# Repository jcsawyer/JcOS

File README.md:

Raspberry PI OS Tutorials translated from the Rust tutorials available [here](https://github.com/rust-embedded/rust-raspberrypi-OS-tutorials/tree/master)

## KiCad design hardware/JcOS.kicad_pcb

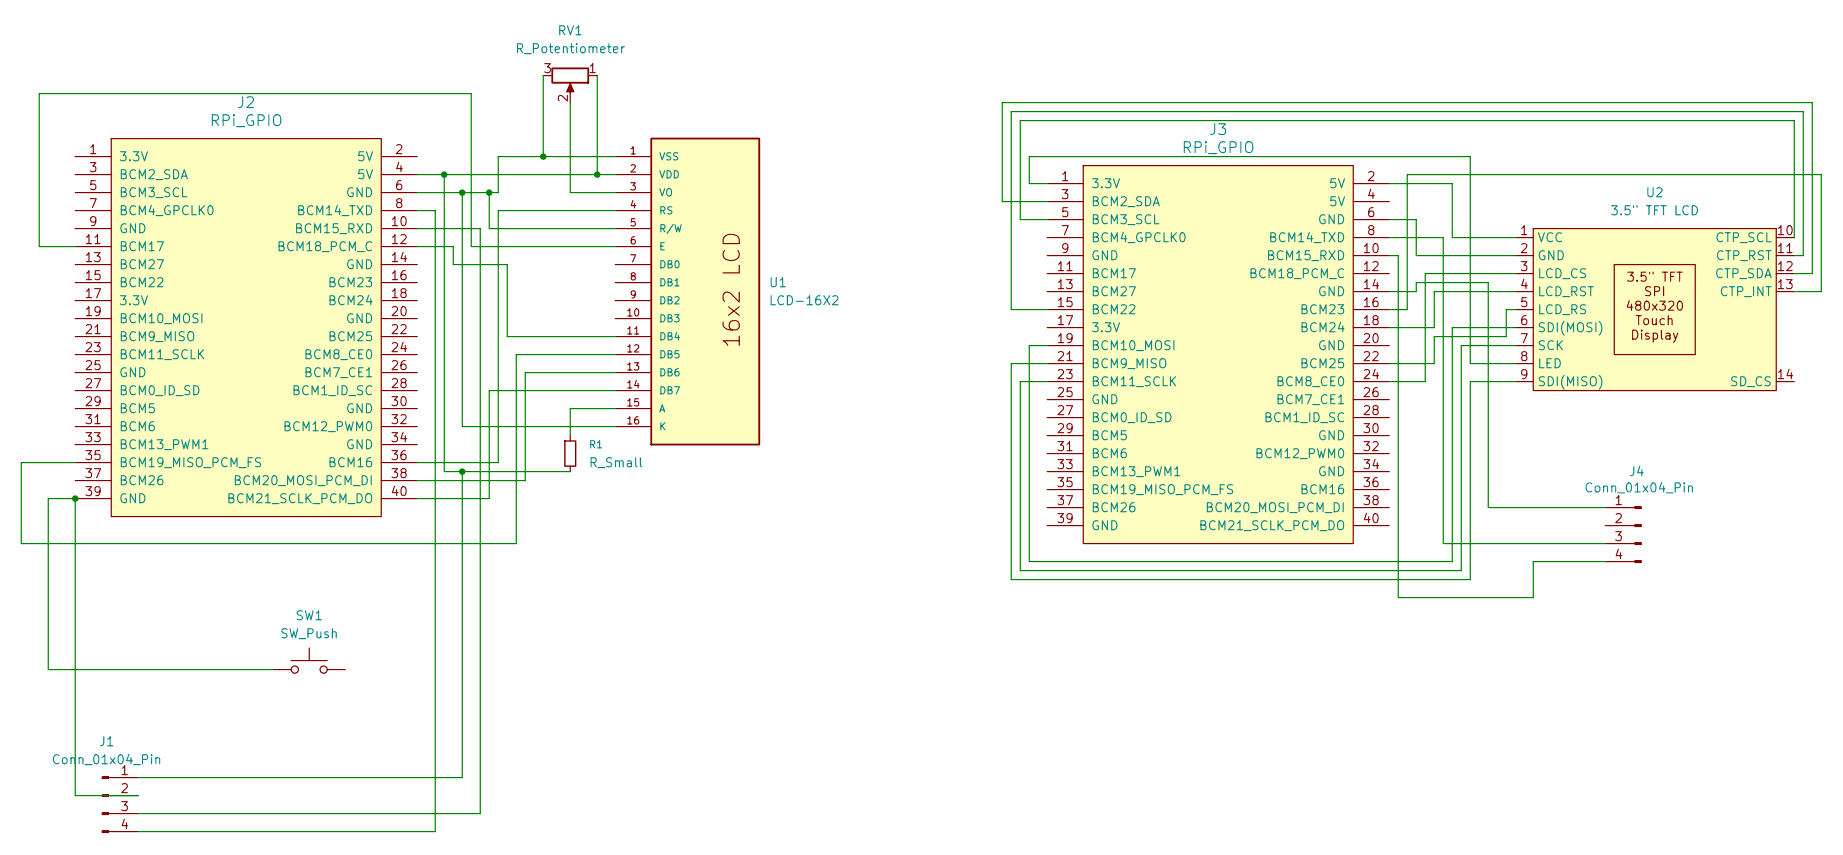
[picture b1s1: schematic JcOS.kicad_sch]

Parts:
J1, J4: Conn_01x04_Pin; PinHeader_1x04_P2.54mm_Vertical
J2, J3: RPi_GPIO; RPI_Hat_B+
R1: R_Small; R_Axial_DIN0309_L9.0mm_D3.2mm_P12.70mm_Horizontal
RV1: R_Potentiometer; Potentiometer_Bourns_3386F_Vertical
SW1: SW_Push; SW_PUSH_6mm
U1: LCD-16X2; MODULE_LCD-16X2; PARTREV N/A
U2: 3.5" TFT LCD; 3.5_ TFT LCD

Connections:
unnamed: J1.1, J2.4 (5V), R1.2, RV1.1, U1.2 (VDD)
unnamed: J1.2, J2.39 (GND), SW1.1
unnamed: J1.3, J2.10 (BCM15_RXD)
unnamed: J1.4, J2.8 (BCM14_TXD)
unnamed: J2.36 (BCM16), U1.4 (RS)
unnamed: J2.11 (BCM17), U1.6 (E)
unnamed: J2.12 (BCM18_PCM_C), U1.11 (DB4)
unnamed: J2.35 (BCM19_MISO_PCM_FS), U1.12 (DB5)
unnamed: J2.38 (BCM20_MOSI_PCM_DI), U1.13 (DB6)
unnamed: J2.40 (BCM21_SCLK_PCM_DO), U1.14 (DB7)
unnamed: J3.3 (BCM2_SDA), U2.12 (CTP_SDA)
unnamed: J3.5 (BCM3_SCL), U2.10 (CTP_SCL)
unnamed: J3.24 (BCM8_CE0), U2.3 (LCD_CS)
unnamed: J3.21 (BCM9_MISO), U2.9 (SDI(MISO))
unnamed: J3.19 (BCM10_MOSI), U2.6 (SDI(MOSI))
unnamed: J3.23 (BCM11_SCLK), U2.7 (SCK)
unnamed: J3.8 (BCM14_TXD), J4.3
unnamed: J3.10 (BCM15_RXD), J4.4
unnamed: J3.15 (BCM22), U2.11 (CTP_RST)
unnamed: J3.16 (BCM23), U2.13 (CTP_INT)
unnamed: J3.18 (BCM24), U2.4 (LCD_RST)
unnamed: J3.22 (BCM25), U2.5 (LCD_RS)
unnamed: J3.14 (GND), J4.1
unnamed: R1.1, U1.15 (A)
unnamed: J2.6 (GND), RV1.3, U1.1 (VSS), U1.5 (R/W), U1.16 (K)
unnamed: RV1.2, U1.3 (VO)
unnamed: J3.6 (GND), U2.2 (GND)
unnamed: J3.1 (3.3V), U2.8 (LED)
unnamed: J3.2 (5V), U2.1 (VCC)

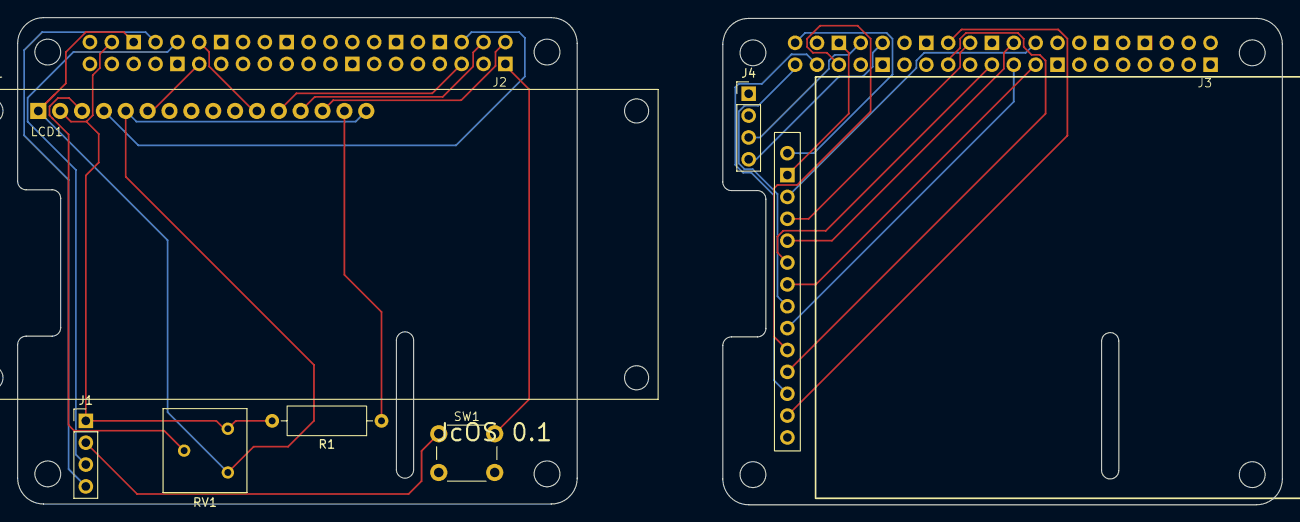
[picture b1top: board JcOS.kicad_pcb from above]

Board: 2 copper layers, 146.9 x 56.6 mm, 10 parts (0 on the bottom side), 29 nets.

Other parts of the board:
U2#2: 3.5_ TFT LCD

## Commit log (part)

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2024-12-21 feat: initial commit
2024-12-22 featL tutorial 04_mailboxes
2024-12-22 feat: lesson 05_uart0
2024-12-22 feat: lesson 06_random
2024-12-22 feat: lesson 07_delays
2024-12-22 feat: lesson 08_power
2024-12-23 feat: lesson 09_framebuffer
2024-12-23 refactor: framebuffer struct
2024-12-24 feat: lesson 0A_pcscreenfont
2024-12-24 fix: missing framebuffer print changes
2024-12-24 feat: lesson 11_exceptions
2024-12-25 refactor: add some build optimizations
2024-12-25 refactor: use for loop in uart_puts
2024-12-26 refactor: add terminal.zig
2024-12-26 wip: terminal print
2024-12-29 fix: get print formatting working
2024-12-29 feat: add time.zig
2024-12-30 cleanup old stuff
2024-12-30 feat: lesson 01_wait_forever
2024-12-31 feat: lesson02_runtime_init
2024-12-31 refactor: replace hardcoded with const to remove duplicate values and unused const
2024-12-31 feat: lesson 03_hacky_hello_world
2024-12-31 refactor: clean up
2025-01-01 wip: lesson 05_drivers_gpio_uart
2025-01-01 feat: wip lesson 05_drivers_gpio_uart
2025-01-02 fix: address space for drivers and attach UART console
2025-01-02 refactor: use console vtable, hook up functions, and cleanup print functions in main
2025-01-02 feat: lesson 07_timestamps
2025-01-03 fix: use c printf for qemu (awaiting testing on real hardware)
2025-01-03 fix: timer adjustments to get things working
2025-01-04 feat: add bc2xxx_rng driver
2025-01-05 feat: initial C++ conversion
2025-01-05 wip: c++
2025-01-05 wip: reset for cleanup
2025-01-05 wip: more c++
2025-01-06 feat get the thing booting properly on real hardware
2025-01-06 refactor: slight cleanup
2025-01-06 feat: re-implemented rng driver
2025-01-06 feat: re-implement rng driver
2025-01-06 feat: and info print and cleanup a little
2025-01-06 feat: implement time
2025-01-06 wip: exception level
2025-01-07 fix: make jump to EL1 in ASM
2025-01-07 feat: lesson 09_privilege_level
2025-01-07 refactor: tidy up a little bit
2025-01-07 refactor: move everything into kernel dir
2025-01-07 fix: point to new location of kernel img
2025-01-09 wip: mmu
2025-01-10 feat: complete 10_virtual_mem_part1_identity_mapping
2025-01-10 clang-format
2025-01-10 feat: 11_exceptions_part1_groundwork
2025-01-10 refactor: remove mailbox and set baudrate to 921600
2025-01-11 refactor: cleanup part 1
2025-01-11 refactor: move _arch to arch
2025-01-11 refactor: move std to libc
2025-01-11 refactor: move printf into libc/stdio
2025-01-11 refactor: organize makefile a little and run clang-format
2025-01-11 refactor: further refactor makefile to isolate arch pieces
2025-01-11 refactor: isolate raspberry pi specific sources in makefile
2025-01-11 refactor: remove arch exception dependency in main
2025-01-11 refactor: remove main dependency on aarch memory and exception
2025-01-11 refactor: remove main's depndency on RaspberryPi namespace
2025-01-12 refactor: remove dependency on raspberry pi from kernel main
2025-01-12 feat: read pi version from board
2025-01-12 refactor: board print info
2025-01-12 feat: add aarch mailbox with raspberry pi implementation
2025-01-12 feat: add timeout to mailbox send/receive
2025-01-13 fix: temporarily disable data caching in SCTLR_EL1 when enabling mmu to fix mailbox
2025-01-13 fix: board type mapping
2025-05-26 wip: 16x2 lcd driver
2025-05-27 wip: further lcd driver
2025-05-27 feat: add raspbootcom to project to allow hot reloading
2025-05-28 fix: lcd driver
2025-05-28 refactor: lcd driver
2025-05-30 wip: working "tasks"
2025-05-31 get irq scheduling working
2025-05-31 fix: get irq scheduling finally working
2025-05-31 refactor: small refactoring
2025-05-31 wip: refactor irq code
2025-05-31 wip: tutorial13: exceptions part 2 peripheral IRQs
2025-06-01 tutorial 13: exceptions part2 peripheral irqs
2025-06-01 fix: default to null console
2025-06-01 fix: get UART RX/TX interrupts working
2025-06-02 feat: format lcd write string
2025-06-05 fix: don't return null terminating string character over uart, return optional without a value
2025-09-25 feat: initial syscalls
2026-04-19 tutorial 14: virtual memory part 2: mmio remap
2026-06-13 feat: add custom chainloader with lcd output
2026-06-13 fix: deploy kernel and run it properly
2026-06-13 tutorial 15: virtual memory part 3: precomputed translation tables
2026-06-13 fix: mmu enablement order with new chainloader
2026-06-13 fix: point chainloader to correct boot asm
2026-06-13 feat: increase baud rate back to 921_600 for speed
2026-06-13 fix: comment out base lcd print to remove stray 0
2026-06-14 feat: tutorial 16 - higher half kernel and remove chainloader el1 transition
2026-06-14 feat: tutorial 17 - kernel symbols
2026-06-14 feat: tutorial 18 - backtracing
2026-06-14 feat: tutorial 19 - kernel heap
2026-06-14 feat: add spi and tft display drivers
2026-06-14 feat: add initial hardware kicad project
2026-06-14 feat: 3.5" SPI TFT LCD hat board
2026-06-14 feat: tutorial 20 - timer callbacks
2026-06-22 feat: reverse LCD PCB and add serial connector
2026-06-22 fix: lcd tft driver finalization
2026-06-22 feat: wire up tft spi lcd
2026-06-23 feat: chainloader tft lcd output
2026-06-25 feat: add initial basic generic spi tft driver and change kernel baud rate
2026-06-25 feat: add tft rotation and fix inverted colours
2026-06-26 feat: memory usage footer task
2026-06-26 feat: add initial ui/interactive shell
2026-06-27 feat: wire up touch events with i2c and touch drivers
